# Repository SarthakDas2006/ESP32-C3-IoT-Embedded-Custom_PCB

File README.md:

# ESP32-C3-IoT-Embedded-Custom_PCB
4-layer ESP32-C3 based custom embedded IoT PCB featuring onboard temperature & humidity, light, and audio sensing, USB Type-C, Li-Po charging, and external flash memory. Designed for smart embedded systems, wireless IoT applications, portable sensing, automation, and edge device prototyping.
A professionally designed 4-layer ESP32-based IoT development board created using KiCad.
This project was developed to explore real-world PCB engineering concepts including multilayer routing, power management, USB-C integration, sensor interfacing, and signal integrity practices.

# 📸 Project Preview

## 3D PCB Render

# 🚀 Features

- ESP32-C3-WROOM module with onboard antenna
- 4-layer PCB stackup
- USB Type-C interface
- Li-Ion battery charging circuit
- Onboard voltage regulation
- SD card interface
- External SPI flash memory
- Temperature and humidity sensor interface
- Photo sensor interface
- Microphone and amplifier circuitry
- Reset and Boot buttons
- Ground plane optimization
- Decoupling and filtering capacitors
- Test points for debugging

# 🧠 PCB Stackup

| Layer | Function |
|---|---|
| Top Layer | Signal Routing |
| Inner Layer 1 | Ground Plane |
| Inner Layer 2 | Power Plane |
| Bottom Layer | Signal Routing |

The multilayer architecture was designed to improve:
- signal integrity
- grounding
- EMI performance
- power distribution

# 🛠️ Tools Used

- KiCad
- NextPCB DFM tool (HQDFM)
- SnapEDA
- ESP32-C3 Ecosystem
- Multiple datasheets

# 🔌 Hardware Blocks

## ESP32-C3 Module
Main microcontroller responsible for:
- WiFi/Bluetooth communication
- sensor interfacing
- data processing
- IoT applications

## USB Type-C Interface
Used for:
- power input
- USB communication
- firmware flashing

Includes:
- filtering capacitors
- protection circuitry
- proper VBUS routing

## Li-Ion Charging Circuit
Portable power management section featuring:
- battery charging
- regulated power delivery
- charging indication circuitry

## SD Card Interface
SPI-based SD card module used for:
- data logging
- external storage
- sensor data recording

## Sensor Interfaces
The PCB includes provisions for:
- temperature and humidity sensing
- ambient light sensing
- audio input through microphone amplifier circuitry

# 📂 Repository Structure

```text
ESP32-C3-IoT-Embedded-Custom-PCB/
│
├── BOM files/
├── Datasheets/
├── Drill files/
├── Gerber files/
├── Images/
├── custom 3d model libraries/
├── custom footprint libraries/
├── custom symbol libraries/
│
├── ESP32_IoT_4-layer_PCB.kicad_pcb
├── ESP32_IoT_4-layer_PCB.kicad_pro
├── ESP32_IoT_4-layer_PCB.kicad_sch
│
└── README.md
```

# 🎯 Project Objectives

This project was built to gain practical experience in:

- multilayer PCB design
- signal routing
- power integrity
- USB-C hardware implementation
- grounding techniques
- schematic hierarchy
- PCB manufacturing workflow

# 🧪 Key Design Considerations

- Ground plane continuity
- Proper decoupling capacitor placement
- Power filtering and stabilization
- Analog and digital section separation
- Pull-up and pull-down resistor implementation
- Modular schematic organization

# 📦 Manufacturing Ready

The project includes:
- PCB layout
- schematic
- Gerber files
- drill files
- BOM support

Compatible with manufacturers such as:
- JLCPCB
- PCBWay
- NextPCB

# 🔮 Future Improvements

- OTA firmware updates
- CAN bus support
- additional onboard sensors
- low-power optimization
- enclosure design
- impedance-controlled routing

# 📚 Learning Outcomes

Through this project, I developed understanding of:

- multilayer PCB stackups
- copper pours and ground planes
- signal routing
- ESP32 hardware integration
- USB-C implementation
- PCB manufacturing workflow
- hardware debugging concepts

# 👨‍💻 Author

**Sarthak Das**  
Electrical and Electronics Engineering Student at VIT Chennai

# ⭐ Support

If you like this project:
- Star the repository
- Fork the project
- Share feedback and suggestions

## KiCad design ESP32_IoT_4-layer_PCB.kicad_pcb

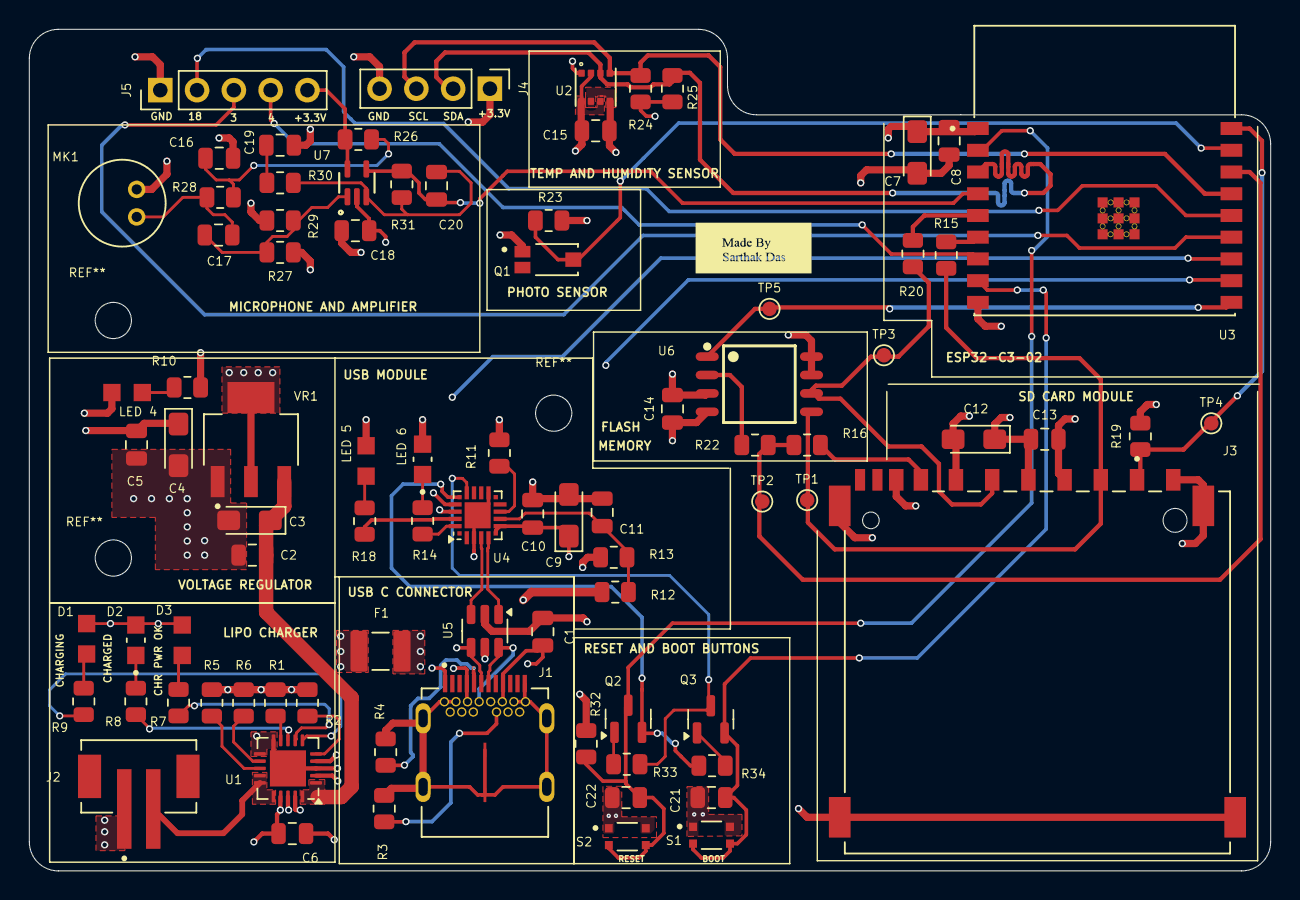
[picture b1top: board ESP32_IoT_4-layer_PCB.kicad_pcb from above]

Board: 4 copper layers, 85.7 x 58.1 mm, 85 parts (0 on the bottom side), 57 nets.

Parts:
C1, C2, C5, C8, C10, C13, C14, C15, C16, C20: 0.1uF; C_0805_2012Metric
C3, C4, C7, C12: 10uF; CP_EIA-3216-18_Kemet-A_Pad1.58x1.35mm_HandSolder
C6, C11, C19, C21, C22: 1uF; C_0805_2012Metric
C9: 4.7uF; CP_EIA-3216-18_Kemet-A_Pad1.58x1.35mm_HandSolder
C17: 10n; C_0805_2012Metric
C18: C; C_0805_2012Metric
D1: LTST-C170KRKT; DIOC200X125X110R
D2: LTST-C170GKT; LED_LTST-C170GKT
D3: LTST-C170TBKT; DIOC200X125X110
F1: 0ZCH0110AF2E; FUSC3225X100N
J1: SS-52400-003; BELFUSE_SS-52400-003
J2: B2B-PH-SM4-TB; JST_B2B-PH-SM4-TB
J3: GSD090012SEU; AMPHENOL_GSD090012SEU
J4: Conn_01x04_Pin; PinHeader_1x04_P2.54mm_Vertical
J5: Conn_01x05_Pin; PinHeader_1x05_P2.54mm_Vertical
LED 4, LED 5: LTST-C170KRKT; DIOC200X125X110R
LED 6: LTST-C170GKT; LED_LTST-C170GKT
MK1: CMC-5042PF-AC; CUI_CMC-5042PF-AC
Q1: TEMT6000X01; TRANS_TEMT6000X01
Q2, Q3: BC817; SOT-23
R1, R2, R19, R23, R30, R33, R34: 10k; R_0805_2012Metric
R3, R4: 5k1; R_0805_2012Metric
R5, R26, R28: 2k; R_0805_2012Metric
R6: 20k; R_0805_2012Metric
R7, R8, R9, R10, R14, R18: 470; R_0805_2012Metric
R11: 1k; R_0805_2012Metric
R12: 22k1; R_0805_2012Metric
R13: 47k5; R_0805_2012Metric
R15, R16, R20, R22: 50; R_0805_2012Metric
R24, R25: 4k7; R_0805_2012Metric
R27, R29: 1M; R_0805_2012Metric
R31: 100k; R_0805_2012Metric
R32: R; R_0805_2012Metric
S1: Boot; SW_USLPT2819DT2TR
S2: Reset; SW_USLPT2819DT2TR
TP1: TestMOSI; TestPoint_Pad_D1.0mm
TP2: TestMISO; TestPoint_Pad_D1.0mm
TP3: TestSCLK; TestPoint_Pad_D1.0mm
TP4: TestCS_DS; TestPoint_Pad_D1.0mm
TP5: TestCS; TestPoint_Pad_D1.0mm
U1: MCP73871; QFN-20-1EP_4x4mm_P0.5mm_EP2.5x2.5mm
U2: BME280; PSON65P250X250X100-8N
U3: ESP32-C3-WROOM-02-H4; MODULE_ESP32-C3-WROOM-02-H4
U4: CP2102N-Axx-xQFN20; SiliconLabs_QFN-20-1EP_3x3mm_P0.5mm_EP1.8x1.8mm
U5: USBLC6-2SC6; SOT-23-6
U6: W25Q32JVSSIQ; SOIC127P790X216-8N
U7: MAX4466EXK; SOT65P210X110-5N
VR1: LM1117MPX-3.3; VREG_LM1117MPX-3.3

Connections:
+3.3V: C4.1, C5.1, C7.1, C8.1, C9.1, C10.2, C12.1, C13.1, C14.1, C15.1, C18.1, J3.4 (VDD1), J4.1, J5.5, LED 4.+, LED 5.+, LED 6.2, R11.1, R19.2, R23.1, R24.1, R25.1, R26.1, R27.1, R32.1, U2.2 (CSB), U2.6 (VDDIO), U2.8 (VDD), U3.1 (3V3), U4.6 (VDD), U4.7 (VREGIN), U6.3 (~WP(IO2)), U6.7 (~HOLD/~RESET(IO3)), U6.8 (VCC), U7.5 (VCC), VR1.2 (VOUT_2), VR1.4 (VOUT_4)
+5V: C2.1, C3.1, U1.1 (OUT), U1.20 (OUT), VR1.3 (VIN)
/+5V_USB: C6.1, D1.+, D2.2, D3.+, F1.2, U1.2 (VPCC), U1.4 (PROG2), U1.17 (CE), U1.18 (IN), U1.19 (IN)
/CHARGED: R8.1, U1.8 (STAT1/~LBO)
/CHARGING: R9.1, U1.6 (~PG)
/CHARGING_POWR_GOOD: R7.1, U1.7 (STAT2)
/ESP32-C3-02/BOOT: C21.1, Q3.2 (E), S1.3, S1.4, U3.8 (IO9)
/ESP32-C3-02/CS: TP5.1, U3.10 (IO10), U6.1 (~CS)
/ESP32-C3-02/CS_SD: J3.1 (CD/DAT3), R19.1, TP4.1, U3.18 (IO0)
/ESP32-C3-02/DTR: Q3.3 (C), R33.1, U4.15 (~CTS)
/ESP32-C3-02/EN: C22.1, Q2.3 (C), R32.2, S2.3, S2.4, U3.2 (EN)
/ESP32-C3-02/GPIO8: J5.4, U3.7 (IO8)
/ESP32-C3-02/GPIO18: J5.3, U3.13 (IO18)
/ESP32-C3-02/GPIO19: J5.2, U3.14 (IO19)
/ESP32-C3-02/MIC_OUT: C20.2, R31.1, U3.4 (IO5), U7.4 (OUT)
/ESP32-C3-02/MISO_DO: R16.2, R22.1, TP2.1, U3.16 (IO2)
/ESP32-C3-02/MOSI_DI: J3.2 (CMD), R15.2, TP1.1, U6.5 (DI(IO0))
/ESP32-C3-02/PHOTO_C: Q1.3, R23.2, U3.17 (IO1)
/ESP32-C3-02/RTS: Q2.2 (E), R34.1, U4.16 (~RTS)
/ESP32-C3-02/RX_TX: U3.12 (TXD), U4.17 (RXD)
/ESP32-C3-02/SCL: J4.3, R24.2, U2.4 (SCK), U3.15 (IO3)
/ESP32-C3-02/SCLK: J3.5 (CLK), R20.1, TP3.1, U6.6 (CLK)
/ESP32-C3-02/SDA: J4.2, R25.2, U2.3 (SDI), U3.3 (IO4)
/ESP32-C3-02/TX_RX: U3.11 (RXD), U4.18 (TXD)
/ESP32-C3-02/USB_D+: U4.4 (D+), U5.3 (I/O2)
/ESP32-C3-02/USB_D-: U4.5 (D-), U5.1 (I/O1)
/PWD_LED: LED 4.-, R10.2
/USB_DN: J1.A7 (DN1), J1.B7 (DN2), U5.6 (I/O1)
/VBAT: J2.2, U1.14 (V_{BAT}), U1.15 (V_{BAT}), U1.16 (V_{BAT_SENSE})
/VBUS: C1.1, F1.1, J1.A4 (VBUSA1), J1.A9 (VBUSA2), J1.B4 (VBUSB1), J1.B9 (VBUSB2), R12.1, U5.5 (VBUS)
GND: C1.2, C2.2, C3.2, C4.2, C5.2, C6.2, C7.2, C8.2, C9.2, C10.1, C11.2, C12.2, C13.2, C14.2, C15.2, C16.1, C18.2, C19.2, C21.2, C22.2, J1.A1 (GNDA1), J1.A12 (GNDA2), J1.B1 (GNDB1), J1.B12 (GNDB2), J1.G1 (GND/SHIELD), J1.G2 (GND/SHIELD), J1.G3 (GND/SHIELD), J1.G4 (GND/SHIELD), J1.S1 (GND/SHIELD), J1.S2 (GND/SHIELD), J1.S3 (GND/SHIELD), J1.S4 (GND/SHIELD), J2.1, J3.3 (VSS1), J3.6 (VSS2), J3.8 (DAT1), J3.9 (DAT2), J3.G1 (SHIELD_GND), J3.G2 (SHIELD_GND), J3.G3 (SHIELD_GND), J3.G4 (SHIELD_GND), J4.4, J5.1, MK1.GND, Q1.1, R1.2, R2.2, R3.2, R4.2, R5.2, R6.2, R10.1, R13.2, R29.2, S1.1, S1.2, S2.1, S2.2, U1.3 (SEL), U1.10 (V_{SS}), U1.11 (V_{SS}), U1.21 (V_{SS}), U2.1 (GND), U2.5 (SDO), U2.7 (GND), U3.9 (GND), U3.19 (GND), U3.20 (GND), U3.21 (GND), U3.22 (GND), U3.23 (GND), U3.24 (GND), U3.25 (GND), U3.26 (GND), U3.27 (GND), U3.28 (GND), U3.29 (GND), U3.30 (GND), U3.31 (GND), U3.32 (GND), U3.33 (GND), U3.34 (GND), U3.35 (GND), U3.36 (GND), U3.37 (GND), U3.38 (GND), U3.39 (GND), U4.3 (GND), U4.12 (GND), U4.21 (GND), U5.2 (GND), U6.4 (GND), U7.2 (GND), VR1.1 (GND)
unnamed: C16.2, R26.2, R28.1
unnamed: C17.1, MK1.OUT, R28.2
unnamed: C19.1, R30.2
unnamed: D1.-, R9.2
unnamed: D2.1, R8.2
unnamed: D3.-, R7.2
unnamed: LED 6.1, R14.2
unnamed: LED 5.-, R18.2
unnamed: J1.A5 (CC1), J1.A6 (DP1), J1.B6 (DP2), R4.1, U5.4 (I/O2)
unnamed: J1.B5 (CC2), R3.1
unnamed: J3.7 (DAT0), R16.1
unnamed: Q2.1 (B), R33.2
unnamed: Q3.1 (B), R34.2
unnamed: R5.1, U1.13 (PROG1)
unnamed: R6.1, U1.12 (PROG3)
unnamed: R2.1, U1.5 (THERM)
unnamed: R1.1, U1.9 (~TE)
unnamed: R20.2, U3.5 (IO6)
unnamed: R15.1, U3.6 (IO7)
unnamed: C11.1, R12.2, R13.1, U4.8 (VBUS)
unnamed: R11.2, U4.9 (~RST)
unnamed: R18.1, U4.19 (~RXT/GPIO.3)
unnamed: R14.1, U4.20 (~TXT/GPIO.2)
unnamed: R22.2, U6.2 (DO(IO1))
unnamed: C17.2, R27.2, R29.1, U7.1 (IN+)
unnamed: C20.1, R30.1, R31.2, U7.3 (IN-)
